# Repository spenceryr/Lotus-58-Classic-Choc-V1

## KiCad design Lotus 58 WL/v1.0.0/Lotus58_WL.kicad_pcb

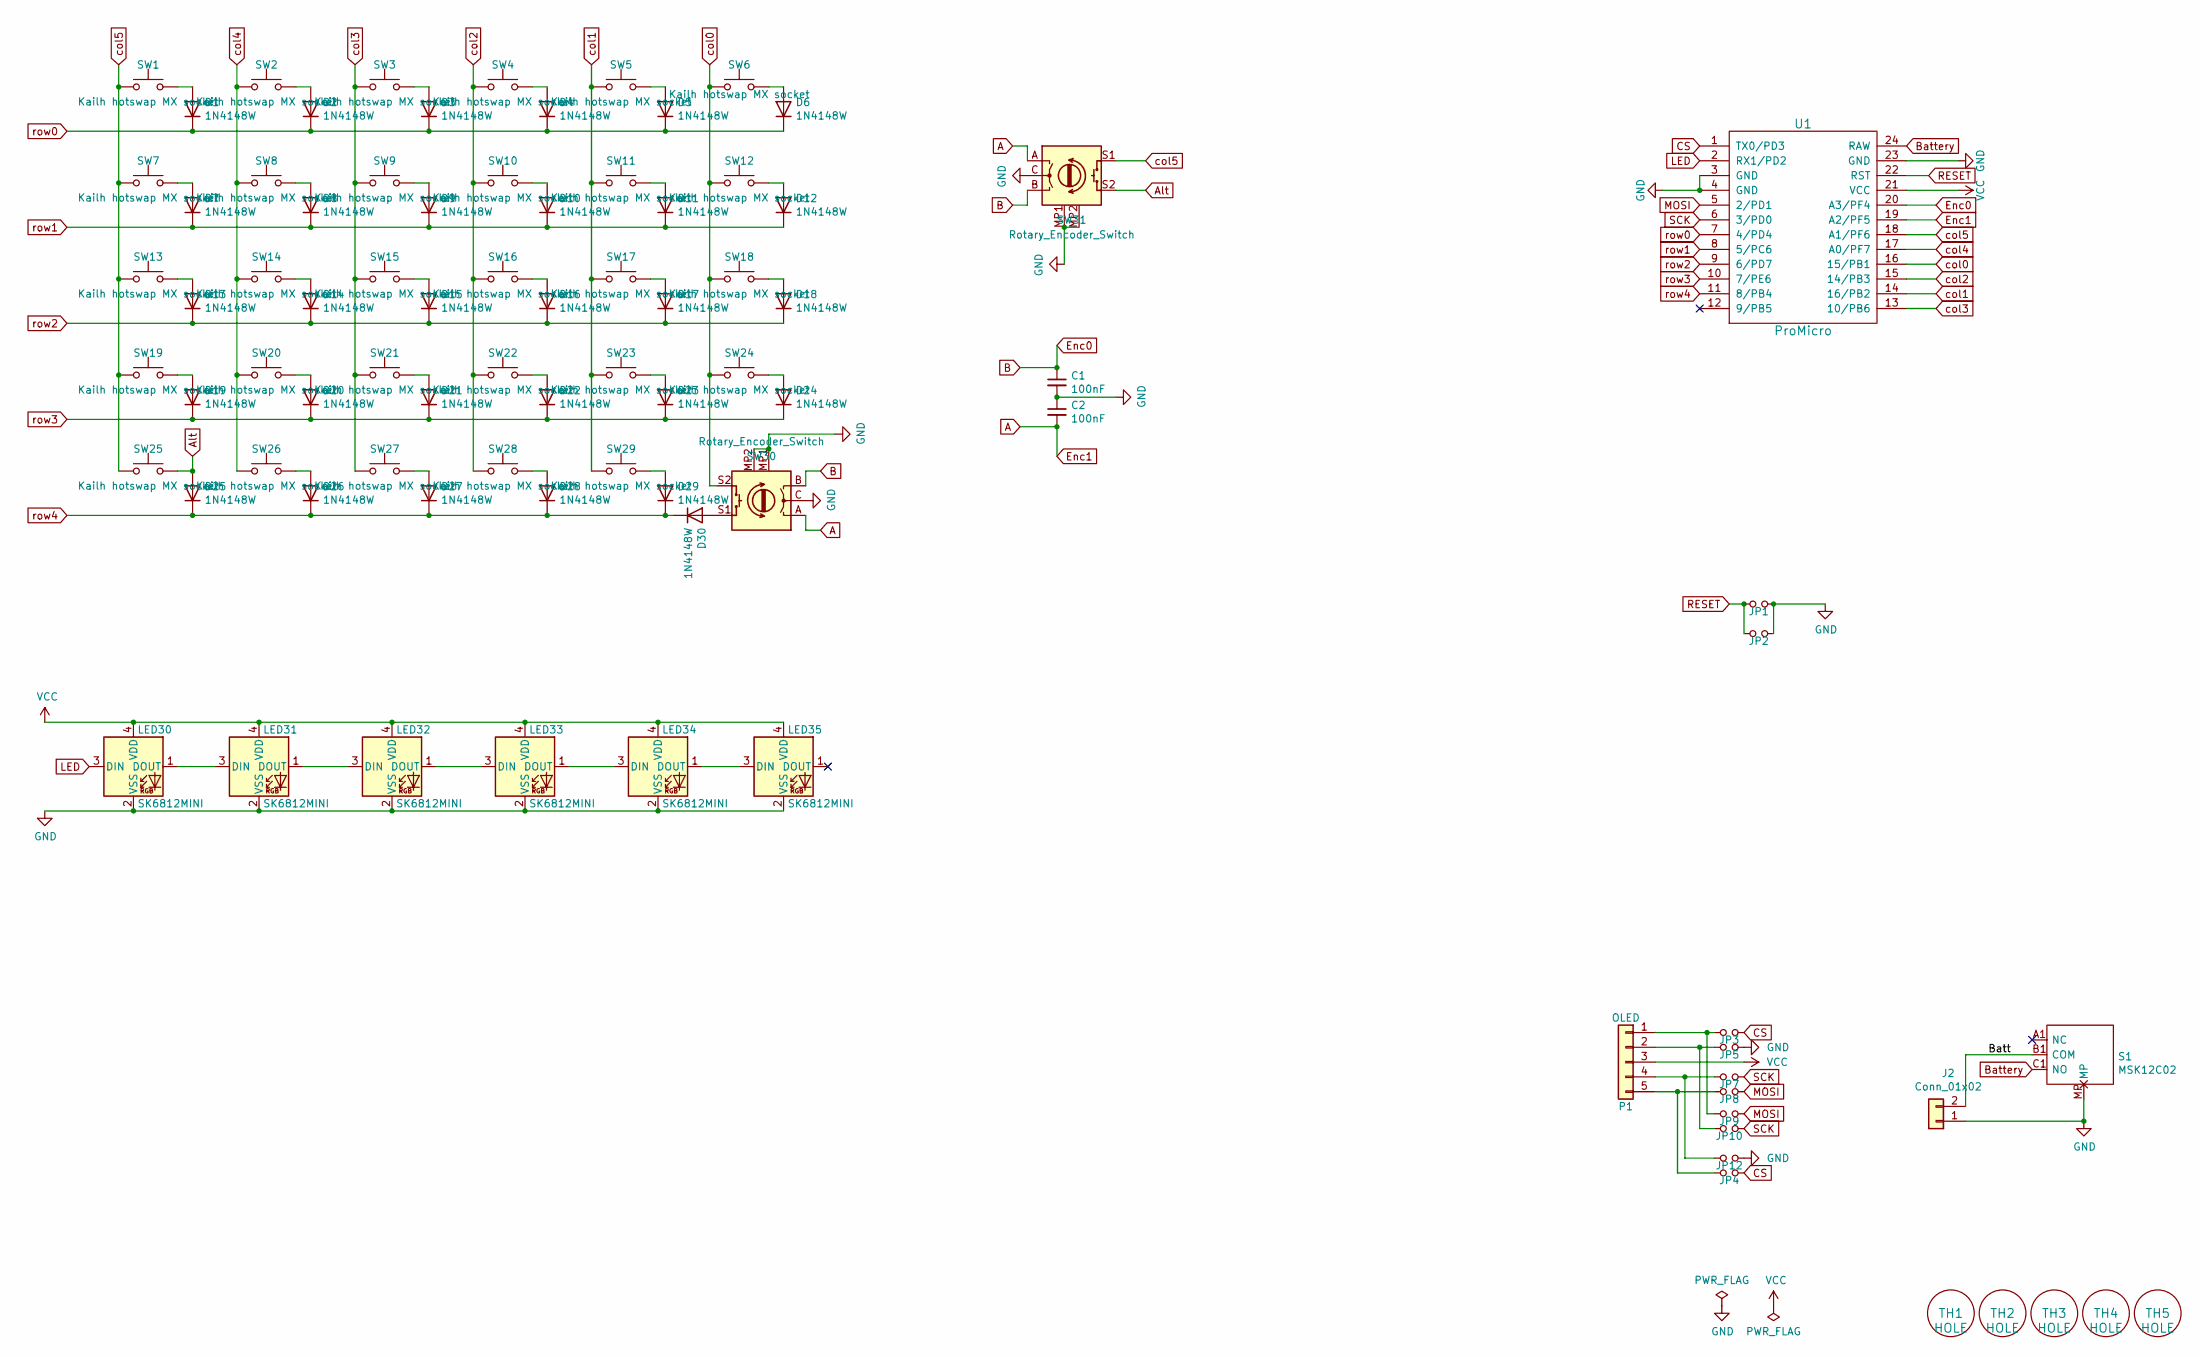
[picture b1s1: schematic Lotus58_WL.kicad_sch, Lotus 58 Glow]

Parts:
C1, C2: 100nF; R_0603_1608Metric_Pad0.98x0.95mm_HandSolder
D1, D2, D3, D4, D5, D6, D7, D8, D9, D10, D11, D12, D13, D14, D15, D16, D17, D18, D19, D20, D21, D22, D23, D24, D25, D26, D27, D28, D29, D30: 1N4148W; D_SOD-123
J2: Conn_01x02; PinHeader_1x02_P2.54mm_Vertical
JP1, JP2: RESET; Jumper_Mini
JP3, JP4, JP5, JP7, JP8, JP9, JP10, JP12: Jumper_NO_Small; Jumper_Mini
LED30, LED31, LED32, LED33, LED34, LED35: SK6812MINI; MX_SK6812MINI-E_REVERSIBLE
P1: OLED; nice!view
S1: MSK12C02; Manufacturer_Part_Number MSK12C02
SW1, SW2, SW3, SW4, SW5, SW6, SW7, SW8, SW9, SW10, SW11, SW12, SW13, SW14, SW15, SW16, SW17, SW18, SW19, SW20, SW21, SW22, SW23, SW24, SW25, SW26, SW27, SW28, SW29: Kailh hotswap MX socket; Kailh_socket_MX_reversible_RGB
SW30: Rotary_Encoder_Switch; RotaryEncoder_Alps_EC11E-Switch_Vertical_H20_special
SW31: Rotary_Encoder_Switch; RotaryEncoder_Alps_EC11E-Switch_Special
TH1, TH2, TH3, TH4, TH5: HOLE; MountingHole_3.7mm
U1: ProMicro; ProMicro_Reversible

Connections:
/Batt: J2.2, S1.B1 (COM)
A: C2.2, SW30.A, SW31.A, U1.19 (A2/PF5)
Alt: D25.2 (A), SW25.2, SW31.S2
B: C1.1, SW30.B, SW31.B, U1.20 (A3/PF4)
Battery: S1.C1 (NO), U1.24 (RAW)
CS: JP3.2, JP4.2, U1.1 (TX0/PD3)
GND: C1.2, C2.1, J2.1, JP1.2, JP2.2, JP5.2, JP12.2, LED30.2 (VSS), LED31.2 (VSS), LED32.2 (VSS), LED33.2 (VSS), LED34.2 (VSS), LED35.2 (VSS), S1.MP, SW30.C, SW30.MP1 (GND), SW30.MP2 (GND), SW31.C, SW31.MP1 (GND), SW31.MP2 (GND), U1.3 (GND), U1.4 (GND), U1.23 (GND)
LED: LED30.3 (DIN), U1.2 (RX1/PD2)
MOSI: JP8.2, JP9.2, U1.5 (2/PD1)
unnamed: D1.2 (A), SW1.2
unnamed: D2.2 (A), SW2.2
unnamed: D3.2 (A), SW3.2
unnamed: D4.2 (A), SW4.2
unnamed: D5.2 (A), SW5.2
unnamed: D6.2 (A), SW6.2
unnamed: D7.2 (A), SW7.2
unnamed: D8.2 (A), SW8.2
unnamed: D9.2 (A), SW9.2
unnamed: D10.2 (A), SW10.2
unnamed: D11.2 (A), SW11.2
unnamed: D12.2 (A), SW12.2
unnamed: D13.2 (A), SW13.2
unnamed: D14.2 (A), SW14.2
unnamed: D15.2 (A), SW15.2
unnamed: D16.2 (A), SW16.2
unnamed: D17.2 (A), SW17.2
unnamed: D18.2 (A), SW18.2
unnamed: D19.2 (A), SW19.2
unnamed: D20.2 (A), SW20.2
unnamed: D21.2 (A), SW21.2
unnamed: D22.2 (A), SW22.2
unnamed: D23.2 (A), SW23.2
unnamed: D24.2 (A), SW24.2
unnamed: D26.2 (A), SW26.2
unnamed: D27.2 (A), SW27.2
unnamed: D28.2 (A), SW28.2
unnamed: D29.2 (A), SW29.2
unnamed: D30.2 (A), SW30.S1
unnamed: JP3.1, JP9.1, P1.1
unnamed: JP5.1, JP10.1, P1.2
unnamed: JP7.1, JP12.1, P1.4
unnamed: LED30.1 (DOUT), LED31.3 (DIN)
unnamed: LED31.1 (DOUT), LED32.3 (DIN)
unnamed: LED32.1 (DOUT), LED33.3 (DIN)
unnamed: LED33.1 (DOUT), LED34.3 (DIN)
unnamed: LED34.1 (DOUT), LED35.3 (DIN)
unnamed: JP4.1, JP8.1, P1.5
RESET: JP1.1, JP2.1, U1.22 (RST)
SCK: JP7.2, JP10.2, U1.6 (3/PD0)
VCC: LED30.4 (VDD), LED31.4 (VDD), LED32.4 (VDD), LED33.4 (VDD), LED34.4 (VDD), LED35.4 (VDD), P1.3, U1.21 (VCC)
col0: SW6.1, SW12.1, SW18.1, SW24.1, SW30.S2, U1.16 (15/PB1)
col1: SW5.1, SW11.1, SW17.1, SW23.1, SW29.1, U1.14 (16/PB2)
col2: SW4.1, SW10.1, SW16.1, SW22.1, SW28.1, U1.15 (14/PB3)
col3: SW3.1, SW9.1, SW15.1, SW21.1, SW27.1, U1.13 (10/PB6)
col4: SW2.1, SW8.1, SW14.1, SW20.1, SW26.1, U1.17 (A0/PF7)
col5: SW1.1, SW7.1, SW13.1, SW19.1, SW25.1, SW31.S1, U1.18 (A1/PF6)
row0: D1.1 (K), D2.1 (K), D3.1 (K), D4.1 (K), D5.1 (K), D6.1 (K), U1.7 (4/PD4)
row1: D7.1 (K), D8.1 (K), D9.1 (K), D10.1 (K), D11.1 (K), D12.1 (K), U1.8 (5/PC6)
row2: D13.1 (K), D14.1 (K), D15.1 (K), D16.1 (K), D17.1 (K), D18.1 (K), U1.9 (6/PD7)
row3: D19.1 (K), D20.1 (K), D21.1 (K), D22.1 (K), D23.1 (K), D24.1 (K), U1.10 (7/PE6)
row4: D25.1 (K), D26.1 (K), D27.1 (K), D28.1 (K), D29.1 (K), D30.1 (K), U1.11 (8/PB4)

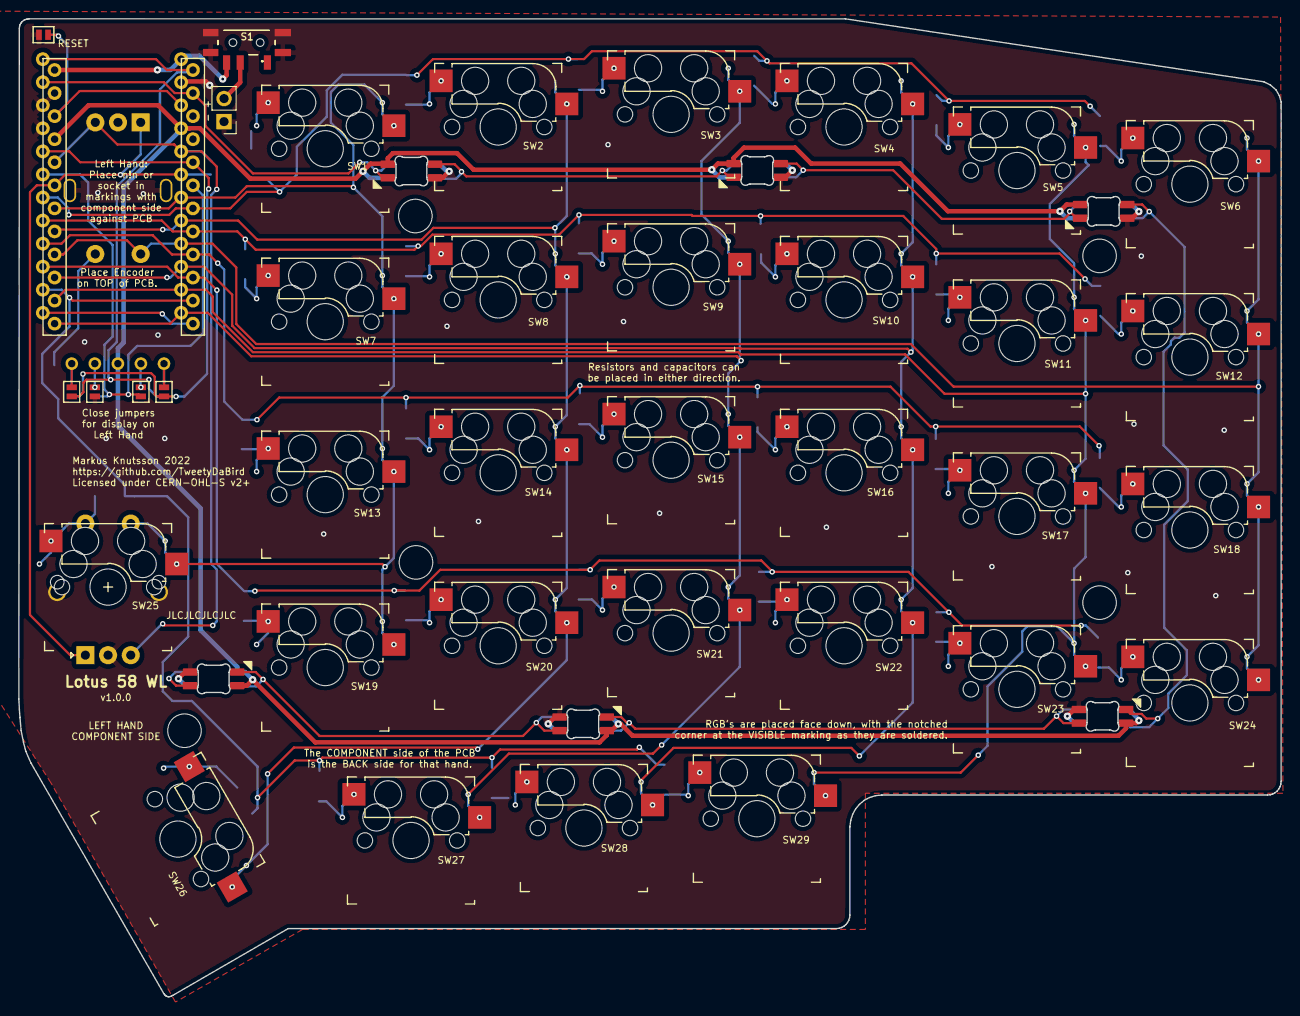
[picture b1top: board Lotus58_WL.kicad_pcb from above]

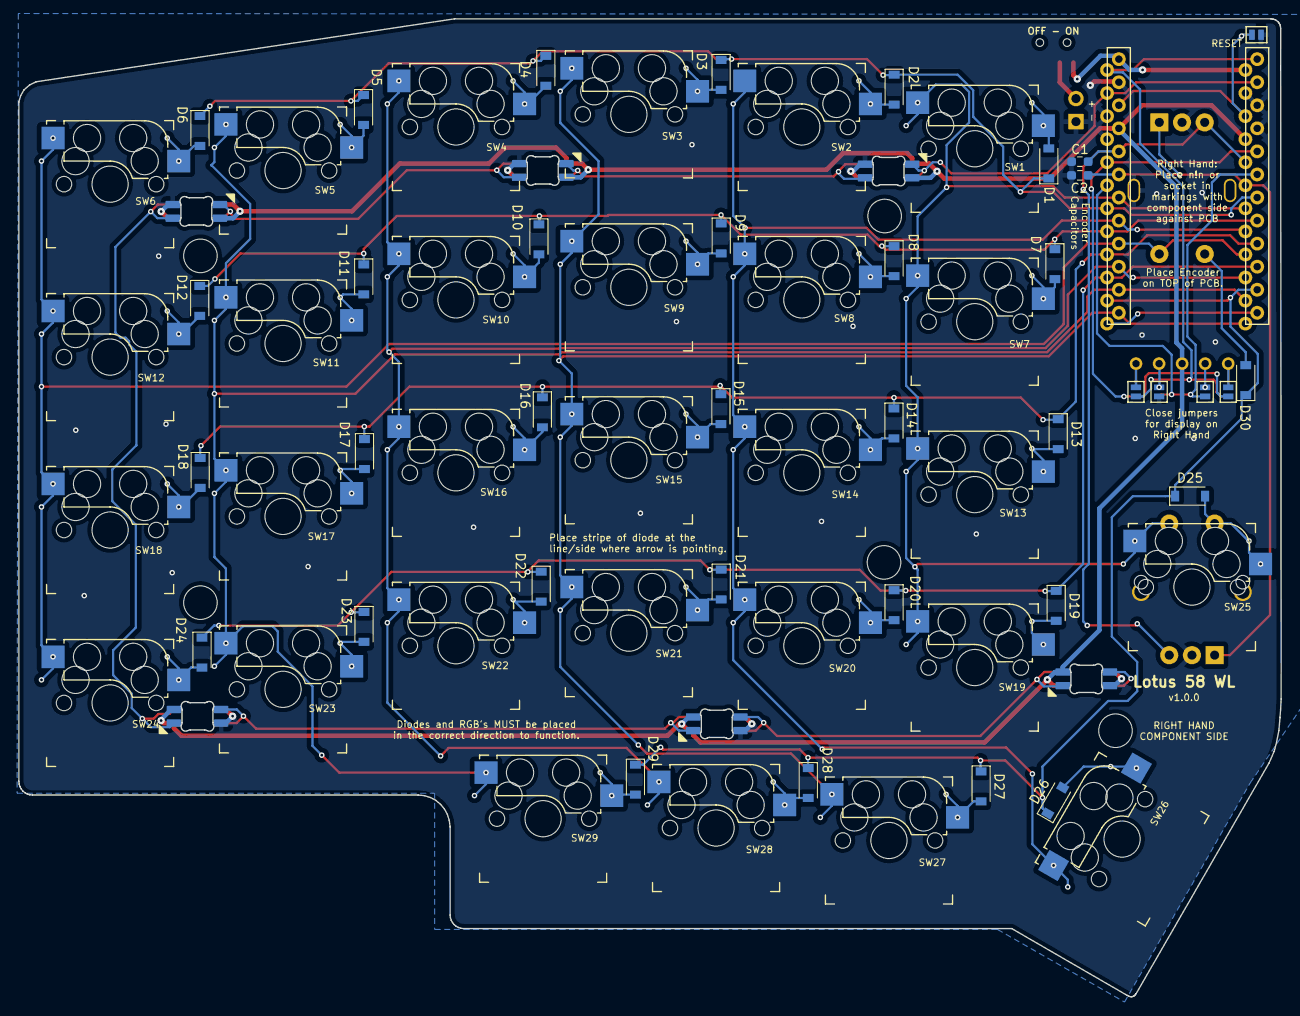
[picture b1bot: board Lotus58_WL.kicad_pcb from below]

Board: 2 copper layers, 139.1 x 107.7 mm, 88 parts (38 on the bottom side), 61 nets.

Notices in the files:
Lotus 58 WL/v1.0.0/Lotus58_WL.kicad_pcb:
Licensed under CERN-OHL-S v2 or any superseding version
